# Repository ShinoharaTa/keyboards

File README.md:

# Shinohara設計キーボード情報

([Click here for the English version of the document.](./LICENSE))

ここには私、Shinoharaの作成したキーボードの情報を記載します。

以下、必要なドキュメント

- [篠原氏の基板設計データ利用規約に関して](./License.md)
- [Amazon 欲しい物リスト](https://www.amazon.co.jp/hz/wishlist/ls/36H4COTLUYA0M?ref_=wl_share)

## BlackMask60 (非売品)

初設計の左右分割 Column Staggardキーボード  
部品点数を削減してシンプルにしつつ耐久性やスイッチ交換可能などのメンテナンス性を確保  
販売はありません。

→後継製品：RURA66

## 素 - Shiro (終売)

2019年の販売開始から2022年まで継続したロングセラー商品
以下でお取り扱いがありました。  

### 販売情報

- [Booth](https://shino3.booth.pm/items/1444895)
- [遊舎工房](https://shop.yushakobo.jp/products/consign_shiro)
- [迷宮商会](https://store.shopping.yahoo.co.jp/meikyuu/gj-kb-201907270001.html)

※現在は終売しました。  
基板のみ販売を継続しています。

### 設計データ

[キーボードの設計データを公開しました。](https://github.com/ShinoharaTa/keyboards/tree/master/Shiro/pcb/Shiro)  
設計データの利用にあたっては、かならず利用規約を読み、同意の上での活用をお願いします。

## 玄 - Kuro

名刺サイズをベースに拡張したキーボード  

- 30%キーボード
- 左右分離式
- 拡張部品で親指対応

## RURA66

BlackMask60ベースに再設計したキーボード

- 左右分離式
- キーソケットなし
- 価格抑えめ
- Backlight LED（オプション）
- OLED（オプション）

### 販売情報

- [Booth](https://booth.pm/ja/items/2643797)

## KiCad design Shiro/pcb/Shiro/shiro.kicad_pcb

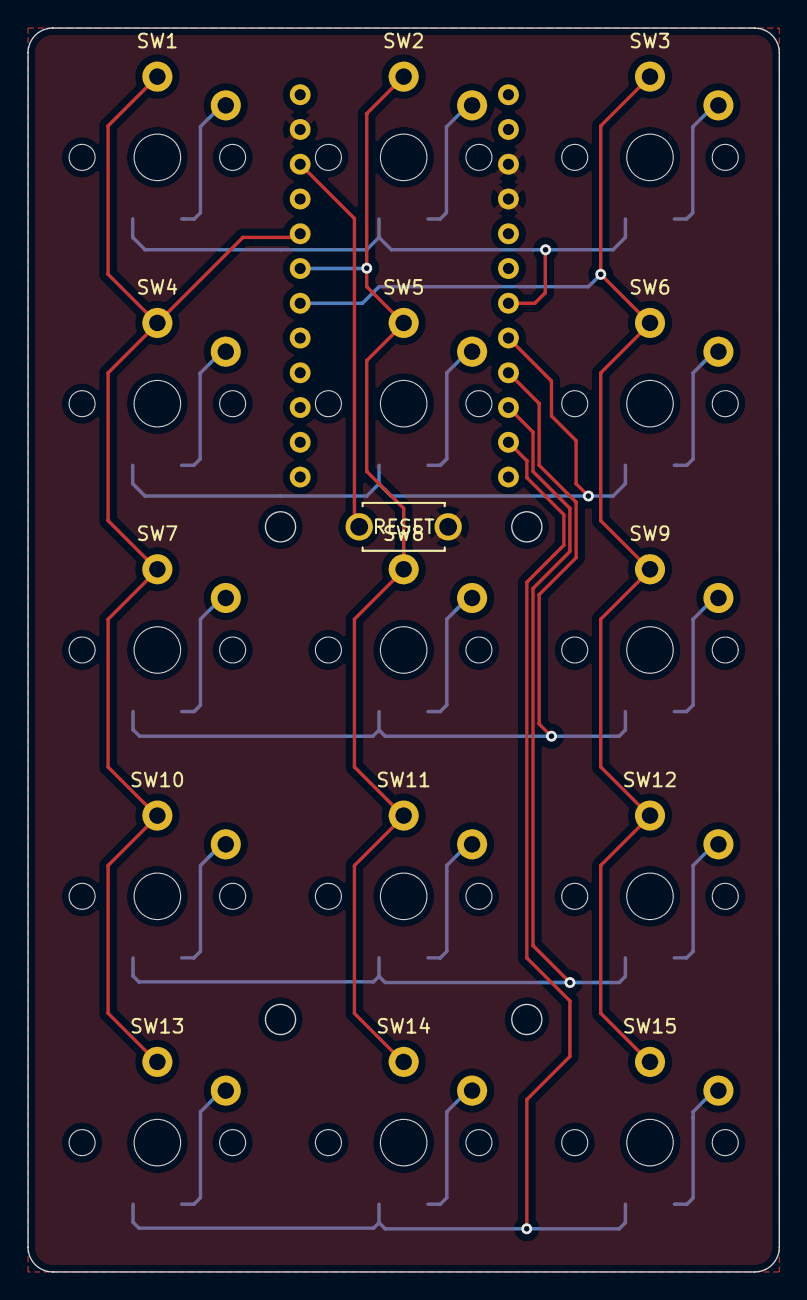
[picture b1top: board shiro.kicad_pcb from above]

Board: 2 copper layers, 54.9 x 90.9 mm, 32 parts (0 on the bottom side), 25 nets.

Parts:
D1, D2, D3, D4, D5, D6, D7, D8, D9, D10, D11, D12, D13, D14, D15: D; D3_SMD_1side
SW1, SW2, SW3, SW4, SW5, SW6, SW7, SW8, SW9, SW10, SW11, SW12, SW13, SW14, SW15: SW_PUSH; SW_kailh_pg1350_1u
SW_RST1: SW_PUSH; ResetSW
U1: ProMicro; ProMicro_v2_1side_Rev

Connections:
GND: SW_RST1.2, U1.3, U1.4, U1.23
unnamed: D1.2, SW1.2
unnamed: D2.2, SW2.2
unnamed: D3.2, SW3.2
unnamed: D4.2, SW4.2
unnamed: D5.2, SW5.2
unnamed: D6.2, SW6.2
unnamed: D7.2, SW7.2
unnamed: D8.2, SW8.2
unnamed: D9.2, SW9.2
unnamed: D10.2, SW10.2
unnamed: D11.2, SW11.2
unnamed: D12.2, SW12.2
unnamed: D13.2, SW13.2
unnamed: D14.2, SW14.2
unnamed: D15.2, SW15.2
Reset: SW_RST1.1, U1.22
col0: SW1.1, SW4.1, SW7.1, SW10.1, SW13.1, U1.20
col1: SW2.1, SW5.1, SW8.1, SW11.1, SW14.1, U1.19
col2: SW3.1, SW6.1, SW9.1, SW12.1, SW15.1, U1.18
row0: D1.1, D2.1, D3.1, U1.7
row1: D4.1, D5.1, D6.1, U1.8
row2: D7.1, D8.1, D9.1, U1.9
row3: D10.1, D11.1, D12.1, U1.10
row4: D13.1, D14.1, D15.1, U1.11

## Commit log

2019-05-20 BlackMasK60のビルドガイド記述はじめ。
2019-05-20 本来はMeishiのビルドガイドでした。書き直し
2019-05-20 Blackmask60 マニュアル追加
2019-05-25 メモ書きレベルのビルドガイド
2019-05-25 トップ画像追加
2019-05-25 Firmwareに関して記載追加
2019-07-07 Shiroのビルドガイドを追加
2019-07-16 ファームウェア書き込み手順を記載
2019-08-22 ビルドガイドの不明箇所を明確化
2019-08-22 BlackMask60のFirmware追加する
2019-11-29 Kuro ビルドガイドとりあえず書いた
2019-11-29 内容修正
2019-12-04 ファームウェア公開
2020-12-30 RURA66組み立てマニュアルを掲載
2021-01-11 RURA66の画像リソース追加と文面修正
2021-01-11 Shiroのビルドガイド誤字修正
2021-01-13 拡張子変更
2021-01-13 ビルドガイド修正
2021-01-13 KeyMap画像を差し替え
2021-06-04 マニュアルにお問い合わせ先を追記
2022-08-09 Shiro PCBを追加
2022-08-10 V6対応
2022-12-12 Readme.md修正とライセンス表記を追加
2022-12-12 Create LICENSE
2022-12-12 ライセンス周り修正
2022-12-13 表記修正
